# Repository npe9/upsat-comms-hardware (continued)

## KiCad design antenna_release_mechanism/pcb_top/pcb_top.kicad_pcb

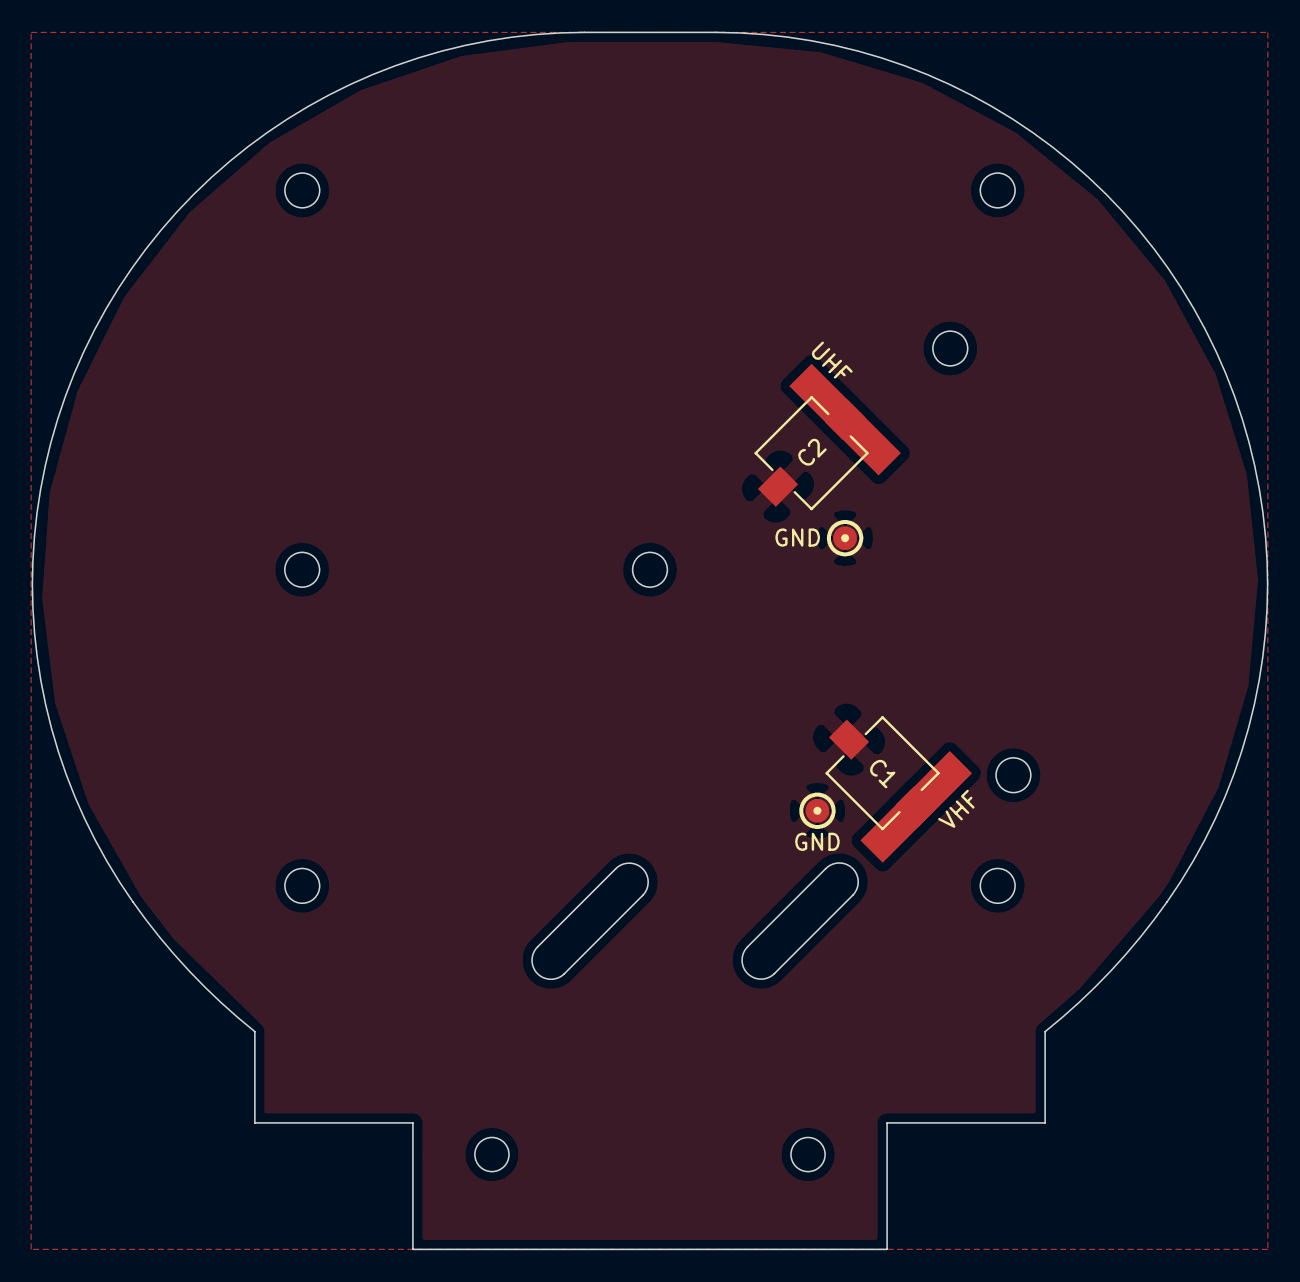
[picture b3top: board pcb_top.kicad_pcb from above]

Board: 2 copper layers, 78.2 x 77.0 mm, 6 parts (0 on the bottom side), 2 nets, no tracks yet.

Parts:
C1, C2: CTRIM; murata-dzb4-b
GND: RFSHL-145; testpoint_1mm5
GND#2: RFSHL-437; testpoint_1mm5
UHF: RFSTR-437; rfstrip-144
VHF: RFSTR-145; rfstrip-144

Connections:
GND: C1.2, C2.2, GND.1, GND#2.1
VCOM: C1.1, C2.1, UHF.1, VHF.1

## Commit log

2016-02-09 Initial commit including README LICENSE and .gitignore files.
2016-02-09 First commit for antenna release mechanism.
2016-02-16 [WIP] Upsat COMMS PCB
2016-03-13 Add KiCad libs for upsat-comms-hardware.
2016-03-15 Add up to date files before final tests.
2016-03-21 Fix lidFR4 to prevent colision with sensor holder parts.
2016-03-28 Add latest changes to sinc with kikad antenna matching design.
2016-03-30 Add PCB top design.
2016-03-30 GPS bottom PCB of ANT.
2016-03-30 Update PCB based on PTFE outline.
2016-04-08 [WIP] 4 layer restructuring of COMMS.
2016-04-09 Cleanup of zones and vias.
2016-04-09 Restructuring libraries.
2016-04-09 Create silkscreen and reroute OBC Connector.
2016-04-09 Cleanup schematic.
2016-04-09 Add vias on PA.
2016-04-10 Recreate zones for In2.
2016-04-10 New footprint for RF5110G.
2016-04-10 Routing changes and package fixes.
2016-04-10 Fix silkscreen specs.
2016-04-10 Exchange SOT23-5 footprint.
2016-04-11 Fix Taiyo Yuden bead footprint and placement.
2016-04-22 add gerber and sch pdf
2016-04-26 ANT bottom antenna for GPS housing and melt line.
2016-05-05 add RF values for CC1120 RX, wrong path for mmcx con.
2016-05-06 add power amp RF out component values, add comments on CC1120 TXCO-Crystal section, add comments on CC1120 regulator-bead
2016-05-06 Edit OPA R53 resistor
    It should be 180 Ohms to feed P.A AGC with 2.75 Volts.
2016-05-06 Add CC1120 bead part number
2016-05-07 Add values for P.A RF Out matching network
2017-02-28 add .dat to git ignore
2017-02-28 Add UPSat RF simulations from Qucs [WIP]
2022-07-05 add bom
